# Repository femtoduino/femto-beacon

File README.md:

# femto-beacon
FemtoBeacon - Atmel SAM R21 (ARM Cortex M0+, SAM D21 with built in AT86RF233)

To contribute work, please do the following:

 - Fork https://github.com/femtoduino/femto-beacon
 - Checkout your fork of femto-beacon to your machine. You should now have something like `https://github.com/<your_username>/femto-beacon`
 - Add the femtoio/femto-beacon repository as the 'upstream' remote repository of your fork.

```
# Inside the checkout of your fork, add us as the remote repository named 'upstream'
git remote add upstream https://github.com/femtoduino/femto-beacon.git

# Remember to fetch from upstream to get all branch information
git fetch upstream
```

Now, you can pull the latest changes from 'upstream' into your fork, and push all work to your own fork
```
# To list branches.
git branch -a

# To pull changes from upstream 'master' branch into your 'master' branch (assuming you're in the master branch already)
git pull upstream master

# To switch into an existing branch named 'develop'
git checkout develop

# To create a new branch based on the develop branch
git checkout develop
# ...then, make sure you get the latest from upstream
git pull upstream develop
# ...now, create your new branch.
git checkout -b my-new-branch

# To push your new branch to your github fork
git push origin my-new-branch
```

...Once you push your changes to your fork, you may submit a Merge Request via github.
We will review and assess the changes before accepting or rejecting your changes.

## Requirements

For Arduino support, see https://github.com/femtoduino/ArduinoCore-atsamd21e18a/

For bare-metal programming, see below.

On Ubuntu machines, you will need Terry Guo's arm-none-eabi-* toolchain, along with the build-essentials package, openocd 0.9.x with cmsis-dap and hidapi-libusb enabled, and the BOSSA utility.

See the following on how to build OpenOCD on your machine: https://github.com/RIOT-OS/RIOT/wiki/OpenOCD
You must assert the required libraries are installed on your machine.

Compile OpenOCD with the following flags to enable cmsis-dap and hidapi support:
```
# Inside the openocd source code folder...
./configure --enable-maintainer-mode --enable-cmsis-dap --enable-hidapi-libusb
make
sudo make install
```

Install Eclipse C++, and the GNU ARM Eclipse plugins.

Install the BOSSA utility.

See https://github.com/shumatech/BOSSA

## Setup
Download the Atmel Software Framework into the libraries/ folder before compiling examples.
If you have the Atmel Software framework files in a directory named `asf-3.21.0`, then you would need it as `femto-beacon/libraries/asf-3.21.0`

Symlink the boards/femtobeacon folder into your copy of the ASF framework (libraries/asf-x.xx.x/sam0/boards/femtobeacon).
Symlink the femtoIO MPU9250 library folder into your copy of the ASF framework (libraries/asf-x.xx.x/thirdparty/MPU9250).

You can symlink the femto-beacon examples to your Eclipse workspace folder. For example, if you want to make the 'sam-r21-blink' project availabe in Eclipse:

```
# Use ~ or full path! Do not use ./
ln -s /path/to/femto-beacon/examples/sam-r21-blink /path/to/eclipse/workspace/sam-r21-blink
```

...Refresh the Project Explorer panel to view it as a project.

Update the example's config.mk file accordingly
```
# Path to top level ASF directory relative to this project directory.
PRJ_PATH = ../../libraries/asf-3.21.0
```

Then, open up the example in Eclipse, and build. This should generate a BIN file you can then upload to your board using the BOSSA shell.

## How to create a new project
Create a new C project in Eclipse, symlink the libraries/ folder from femto-beacon/libraries into your project's directory.
```
cd MyNewProject/
ln -s /path/to/femto-beacon/libraries libraries
```
You can then copy/modify the asf.h, config.mk, and Makefile into your new project. Remember to modify config.mk to include the paths of the ASF modules you wish to use.

## FemtoBeacon BT support (Nordic nRF52832 Bluetooth 4.2 + NFC, ARM Cortex M4L)
This board is unreleased at this time. These notes are here for future use.
For toolchain setup, see https://devzone.nordicsemi.com/tutorials/7/

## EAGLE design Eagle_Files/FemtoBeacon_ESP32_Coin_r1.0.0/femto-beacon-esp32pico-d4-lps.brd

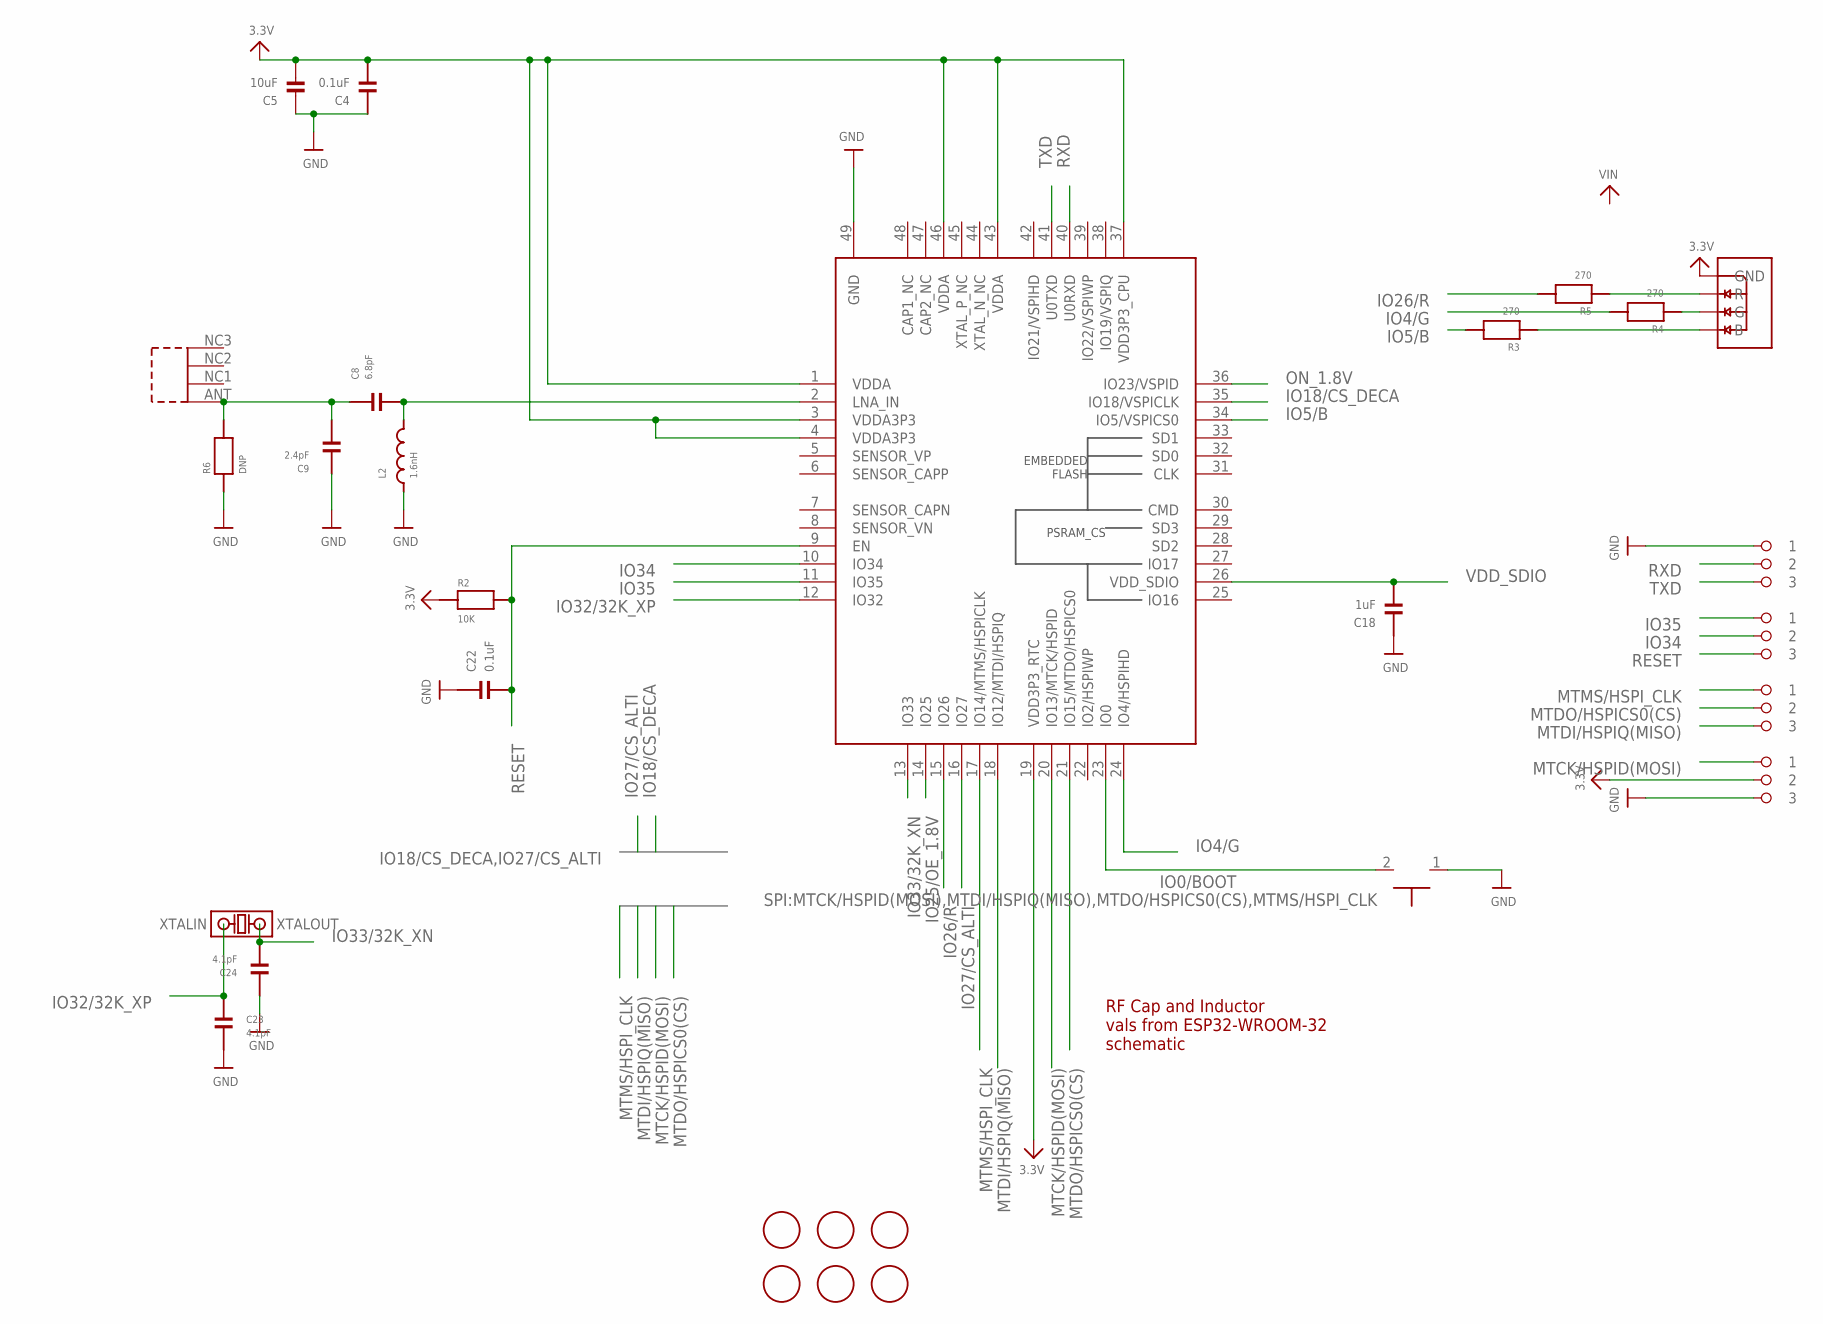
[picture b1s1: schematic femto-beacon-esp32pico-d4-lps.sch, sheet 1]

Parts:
ANT1: 0479480001
BOOT1: TACTILE_SWITCH_NO_GND_NO_BOSS; SIDE_ACT_NO_GND_NO_BOSS
C4, C22: 0.1uF; PART; MPN GRM033C80J104KE84D
C5: 10uF; _0603MP; MPN GRM188R61C106KAALD
C8: 6.8pF; PART; MPN GRM0335C2A6R8DA01D
C9: 2.4pF; PART; MPN GRM0335C1H2R4CA01D
C18: 1uF; PART; MPN CL03A105KQ3CSNH
C23, C24: 4.1pF; PART; MPN GRM0335C1H4R1BA01D
FID1, FID2, FID3, FID4, FID5, FID6: FIDUCIAL; FIDUCIAL_1MM
IC1: ESP32-PICO-D4; ESP32-QFN48_7X7
L2: 1.6nH; PART; MPN LQP03HQ1N6B02D
PIN_EN: 1X3_ROUND
PIN_GPIO_A: 1X3_ROUND
PIN_GPIO_B: 1X3_ROUND
PIN_UART: 1X3_ROUND
R2: 10K; PART; MPN RC0201JR-0710KL
R3, R4, R5: 270; PART; MPN RC0201FR-07270RL
R6: DNP; PART
RGB1: LRTB_R48G
XTAL2: ABS06-107-32.768KHZ-T

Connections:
3.3V: C4.2, C5.2, IC1.1 (VDDA), IC1.3 (VDDA3P3), IC1.4 (VDDA3P3), IC1.19 (VDD3P3_RTC), IC1.37 (VDD3P3_CPU), IC1.43 (VDDA), IC1.46 (VDDA), PIN_GPIO_A.P$2 (2), R2.1, RGB1.1 (GND); also elsewhere on the board
ANT: C8.2, IC1.2 (LNA_IN), L2.2
B_: R3.1, RGB1.4 (B)
GND: BOOT1.1, C4.1, C5.1, C9.1, C18.1, C22.1, C23.1, C24.2, IC1.49 (GND), L2.1, PIN_GPIO_A.P$3 (3), PIN_UART.P$1 (1), R6.1; also elsewhere on the board
G_: R4.1, RGB1.3 (G)
IO0/BOOT: BOOT1.2, IC1.23 (IO0)
IO4/G: IC1.24 (IO4/HSPIHD), R4.2
IO5/B: IC1.34 (IO5/VSPICS0), R3.2
IO18/CS_DECA: IC1.35 (IO18/VSPICLK); also elsewhere on the board
IO25/OE_1.8V: IC1.14 (IO25); also elsewhere on the board
IO26/R: IC1.15 (IO26), R5.2
IO27/CS_ALTI: IC1.16 (IO27); also elsewhere on the board
IO32/32K_XP: C23.2, IC1.12 (IO32), XTAL2.1 (XTALIN)
IO33/32K_XN: C24.1, IC1.13 (IO33), XTAL2.2 (XTALOUT)
IO34: IC1.10 (IO34), PIN_EN.P$2 (2)
IO35: IC1.11 (IO35), PIN_EN.P$1 (1)
MTCK/HSPID(MOSI): IC1.20 (IO13/MTCK/HSPID), PIN_GPIO_A.P$1 (1); also elsewhere on the board
MTDI/HSPIQ(MISO): IC1.18 (IO12/MTDI/HSPIQ), PIN_GPIO_B.P$3 (3); also elsewhere on the board
MTDO/HSPICS0(CS): IC1.21 (IO15/MTDO/HSPICS0), PIN_GPIO_B.P$2 (2); also elsewhere on the board
MTMS/HSPI_CLK: IC1.17 (IO14/MTMS/HSPICLK), PIN_GPIO_B.P$1 (1); also elsewhere on the board
unnamed: ANT1.ANT (1), C8.1, C9.2, R6.2
ON_1.8V: IC1.36 (IO23/VSPID); also elsewhere on the board
RESET: C22.2, IC1.9 (EN), PIN_EN.P$3 (3), R2.2
RXD: IC1.40 (U0RXD), PIN_UART.P$2 (2)
R_: R5.1, RGB1.2 (R)
TXD: IC1.41 (U0TXD), PIN_UART.P$3 (3)
VDD_SDIO: C18.2, IC1.26 (VDD_SDIO)

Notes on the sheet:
RF Cap and Inductor vals from ESP32-WROOM-32 schematic

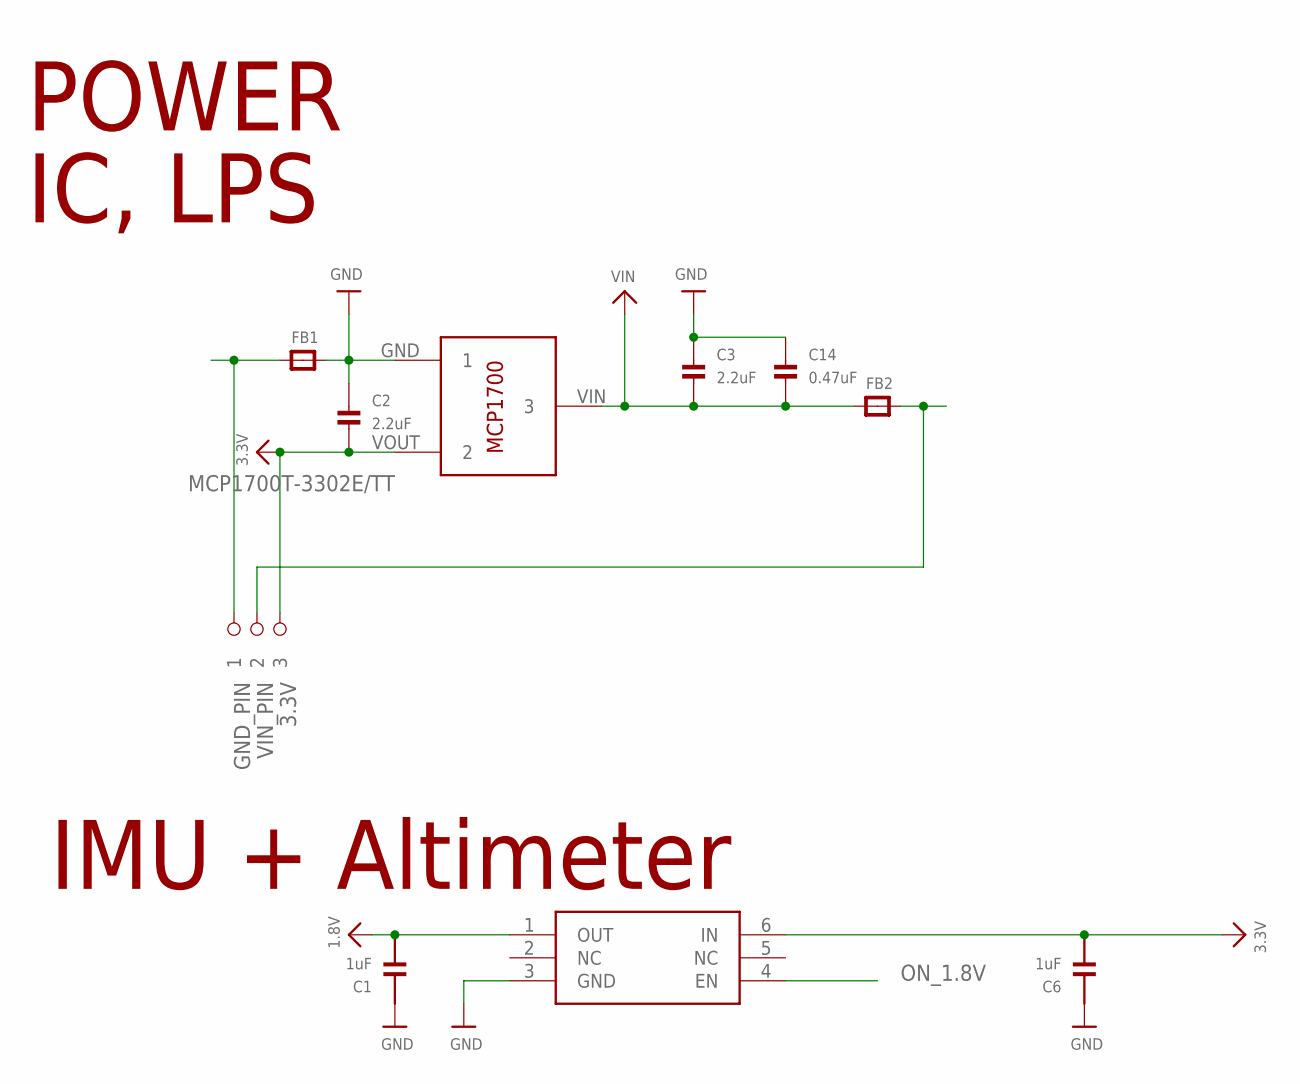
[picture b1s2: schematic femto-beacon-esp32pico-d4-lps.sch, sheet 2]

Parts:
C1, C6: 1uF; PART; MPN CL03A105KQ3CSNH
C2, C3: 2.2uF; _0402MP; MPN C1005X5R0J225K050BC
C14: 0.47uF; _0402MP; MPN GRM155R60J474KE19D
FB1, FB2: FERRITE_0603MP; _0603MP
LDO1: MCP1700T-3302E/TT
LDO1.8V: NCP705MT18TCG; CASE_511BR; MPN NCP705MT18TCG
PIN_PWR: 1X3_ROUND

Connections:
1.8V: C1.2, LDO1.8V.1 (OUT); also elsewhere on the board
3.3V: C2.2, C6.2, LDO1.VOUT (2), LDO1.8V.6 (IN), PIN_PWR.P$3 (3); also elsewhere on the board
GND: C1.1, C2.1, C3.1, C6.1, C14.1, FB1.2, LDO1.GND (1), LDO1.8V.3 (GND); also elsewhere on the board
GND_PIN: FB1.1, PIN_PWR.P$1 (1)
ON_1.8V: LDO1.8V.4 (EN); also elsewhere on the board
VIN: C3.2, C14.2, FB2.1, LDO1.VIN (3)
VIN_PIN: FB2.2, PIN_PWR.P$2 (2)

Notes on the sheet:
POWER
IC, LPS
IMU + Altimeter

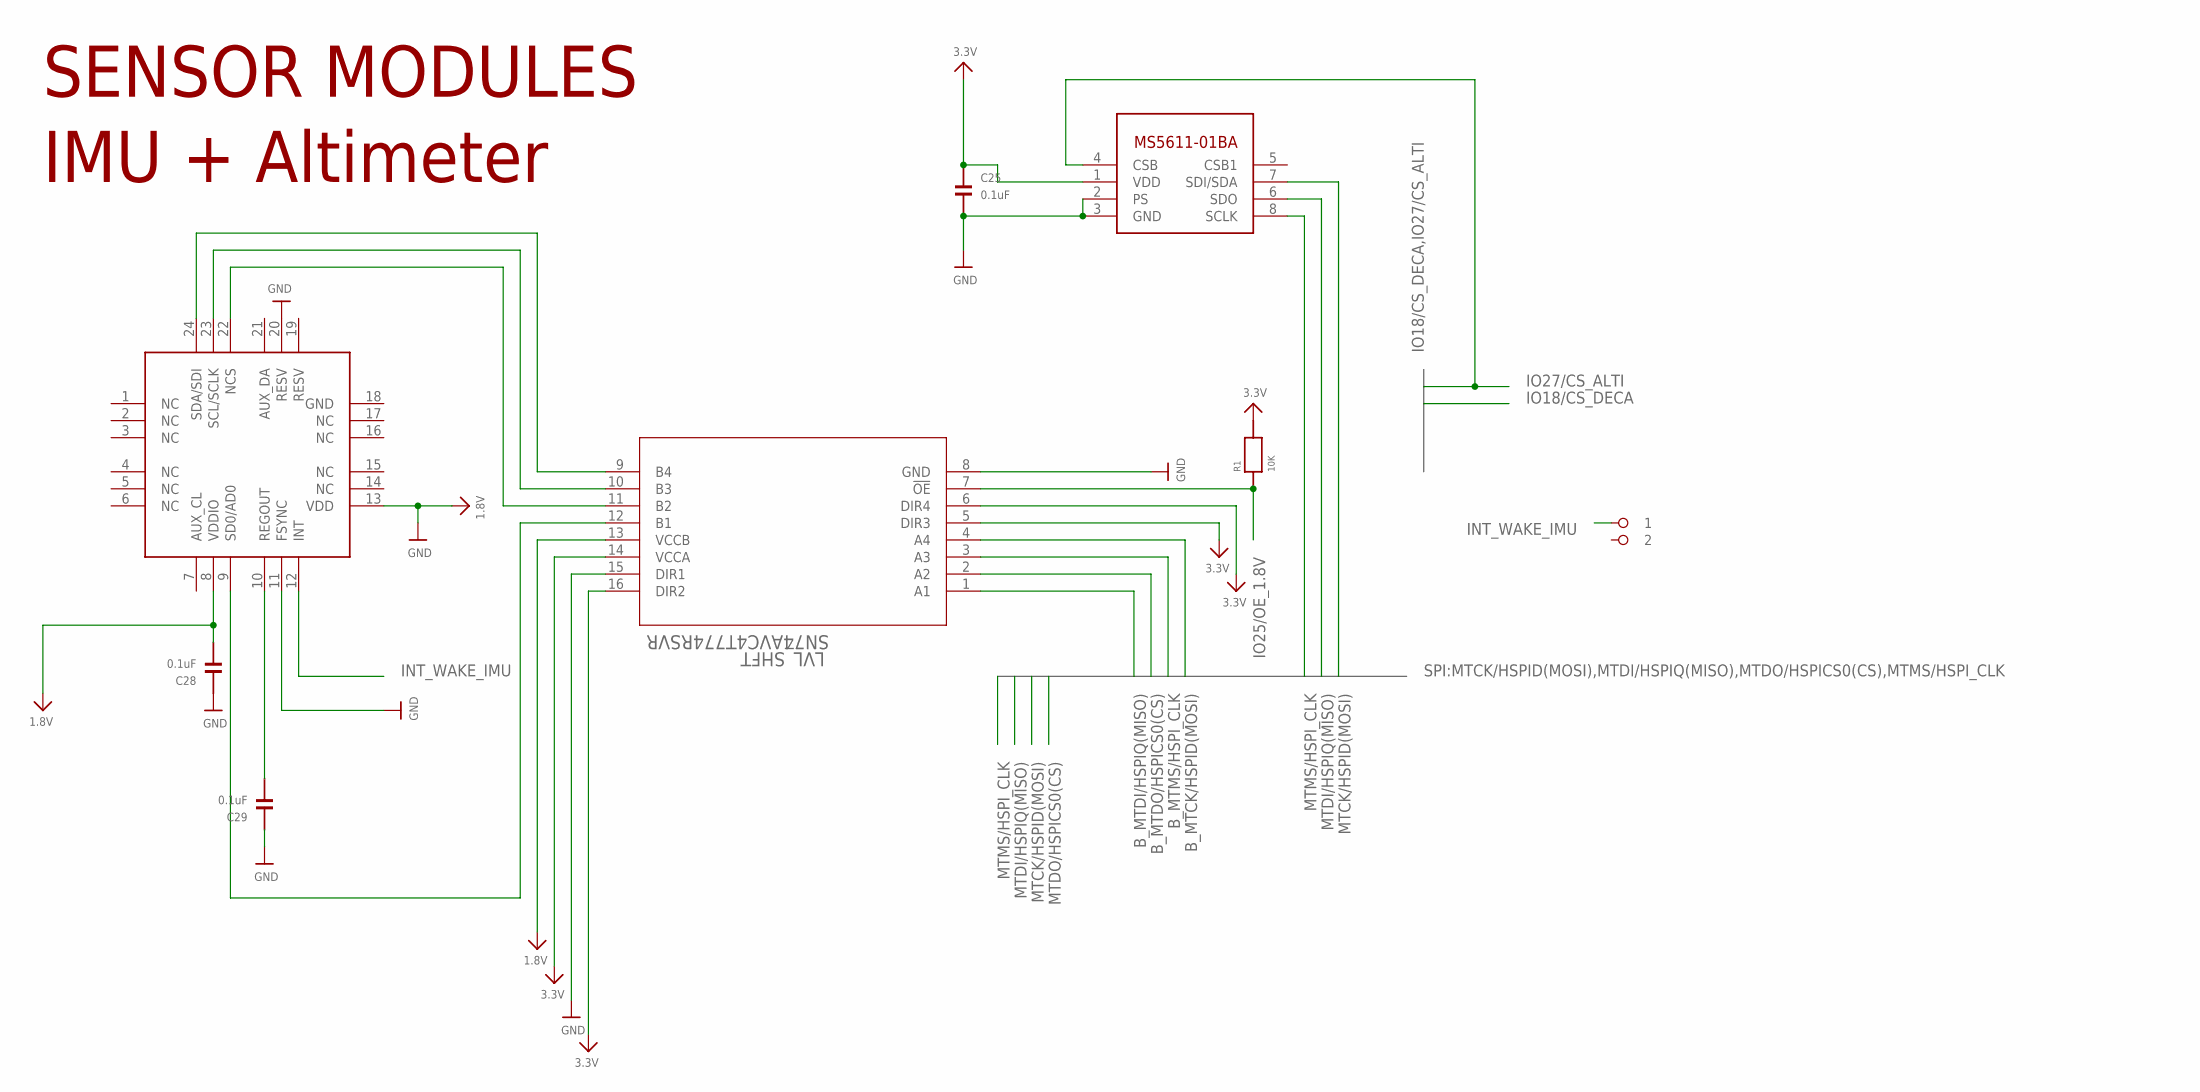
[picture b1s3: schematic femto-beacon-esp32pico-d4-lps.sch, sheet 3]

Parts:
ALT1: MS5611-01BA03; MPN MS561101BA03-50
C25, C28, C29: 0.1uF; PART; MPN GRM033C80J104KE84D
IMU1: ICM-20948; QFN24_3X3
LVL_SHFT: SN74AVC4T774RSVR; RSV16; MPN SN74AVC4T774RSVR
R1: 10K; PART; MPN RC0201JR-0710KL
U$1: 1X2_ROUND

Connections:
1.8V: C28.2, IMU1.8 (VDDIO), IMU1.13 (VDD), LVL_SHFT.13 (VCCB); also elsewhere on the board
3.3V: ALT1.1 (VDD), C25.1, LVL_SHFT.5 (DIR3), LVL_SHFT.6 (DIR4), LVL_SHFT.14 (VCCA), LVL_SHFT.16 (DIR2), R1.2; also elsewhere on the board
B_MTCK/HSPID(MOSI): IMU1.24 (SDA/SDI), LVL_SHFT.9 (B4)
B_MTDI/HSPIQ(MISO): IMU1.9 (SD0/AD0), LVL_SHFT.12 (B1)
B_MTDO/HSPICS0(CS): IMU1.22 (NCS), LVL_SHFT.11 (B2)
B_MTMS/HSPI_CLK: IMU1.23 (SCL/SCLK), LVL_SHFT.10 (B3)
GND: ALT1.2 (PS), ALT1.3 (GND), C25.2, C28.1, C29.1, IMU1.11 (FSYNC), IMU1.18 (GND), IMU1.20 (RESV), LVL_SHFT.8 (GND), LVL_SHFT.15 (DIR1); also elsewhere on the board
INT_WAKE_IMU: IMU1.12 (INT), U$1.P$1 (1)
IO25/OE_1.8V: LVL_SHFT.7 (!OE), R1.1; also elsewhere on the board
IO27/CS_ALTI: ALT1.4 (CSB); also elsewhere on the board
MTCK/HSPID(MOSI): ALT1.7 (SDI/SDA), LVL_SHFT.4 (A4); also elsewhere on the board
MTDI/HSPIQ(MISO): ALT1.6 (SDO), LVL_SHFT.1 (A1); also elsewhere on the board
MTDO/HSPICS0(CS): LVL_SHFT.2 (A2); also elsewhere on the board
MTMS/HSPI_CLK: ALT1.8 (SCLK), LVL_SHFT.3 (A3); also elsewhere on the board
unnamed: C29.2, IMU1.10 (REGOUT)

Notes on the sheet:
SENSOR MODULES
IMU + Altimeter

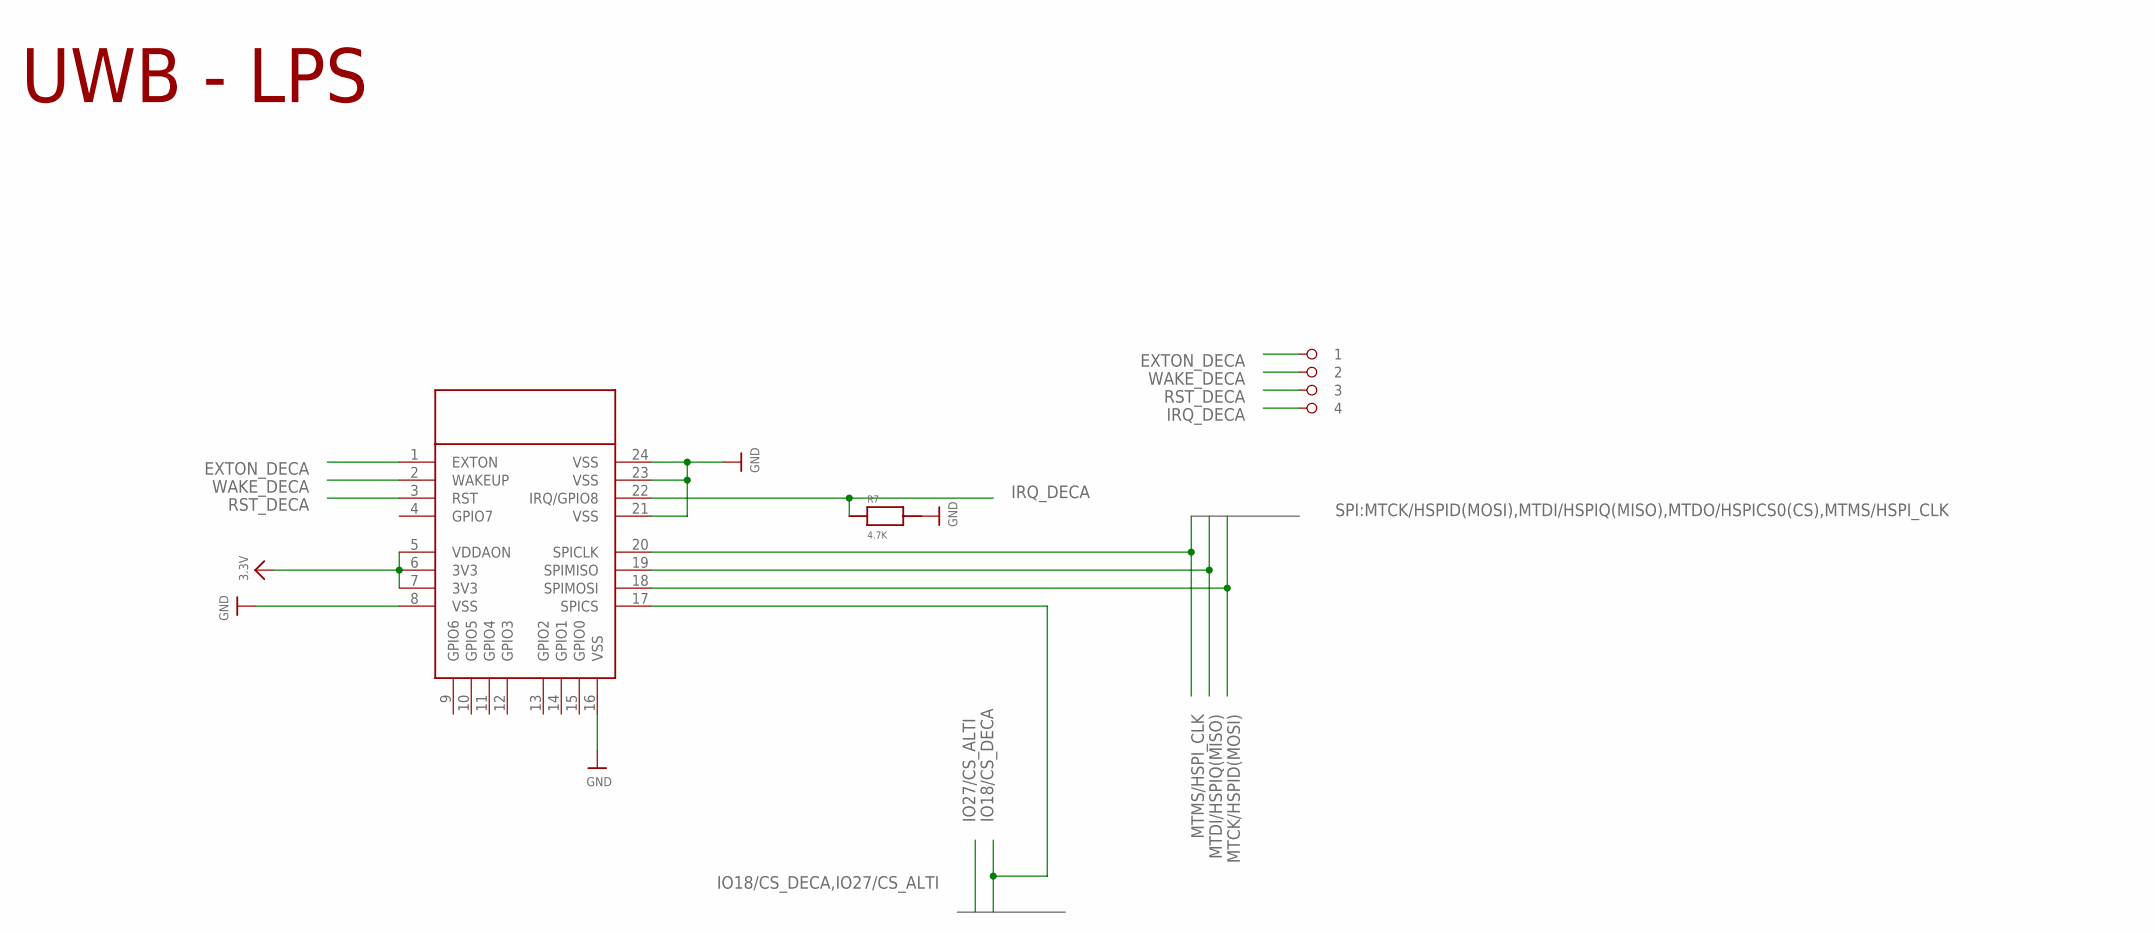
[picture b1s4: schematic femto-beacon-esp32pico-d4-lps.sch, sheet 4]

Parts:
LPS1: DWM100; DWM100_MOD
R7: 4.7K; PART; MPN RC0201FR-074K7L
U$39: 1X4_ROUND

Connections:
3.3V: LPS1.5 (VDDAON), LPS1.6 (3V3), LPS1.7 (3V3); also elsewhere on the board
EXTON_DECA: LPS1.1 (EXTON), U$39.P$1 (1)
GND: LPS1.8 (VSS), LPS1.16 (VSS), LPS1.21 (VSS), LPS1.23 (VSS), LPS1.24 (VSS), R7.2; also elsewhere on the board
IO18/CS_DECA: LPS1.17 (SPICS); also elsewhere on the board
IRQ_DECA: LPS1.22 (IRQ/GPIO8), R7.1, U$39.P$4 (4)
MTCK/HSPID(MOSI): LPS1.18 (SPIMOSI); also elsewhere on the board
MTDI/HSPIQ(MISO): LPS1.19 (SPIMISO); also elsewhere on the board
MTMS/HSPI_CLK: LPS1.20 (SPICLK); also elsewhere on the board
RST_DECA: LPS1.3 (RST), U$39.P$3 (3)
WAKE_DECA: LPS1.2 (WAKEUP), U$39.P$2 (2)

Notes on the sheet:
UWB - LPS

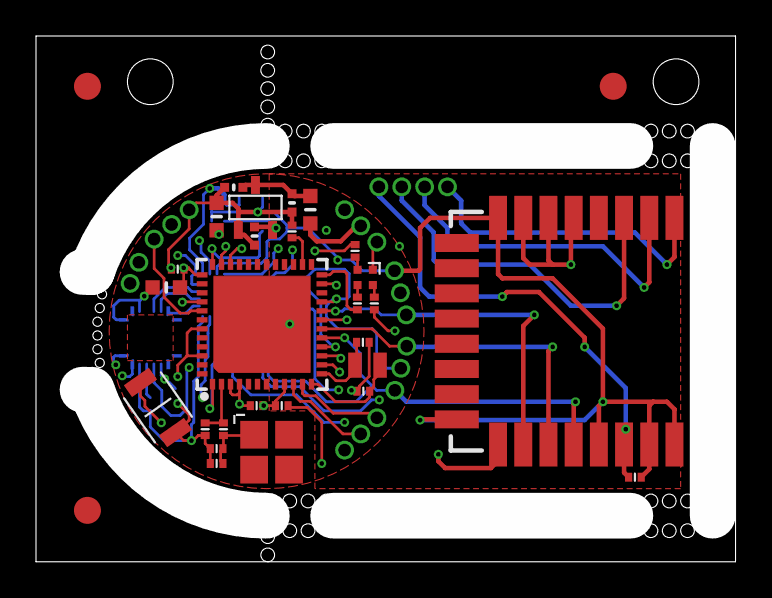
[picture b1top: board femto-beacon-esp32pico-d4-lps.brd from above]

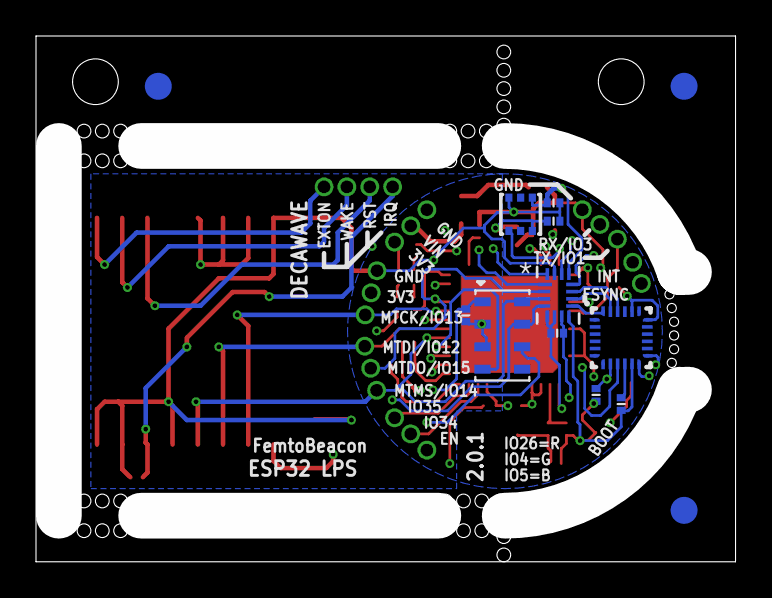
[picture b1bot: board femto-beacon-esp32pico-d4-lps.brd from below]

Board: 4 copper layers, 38.9 x 29.2 mm, 50 parts (13 on the bottom side), 41 nets.

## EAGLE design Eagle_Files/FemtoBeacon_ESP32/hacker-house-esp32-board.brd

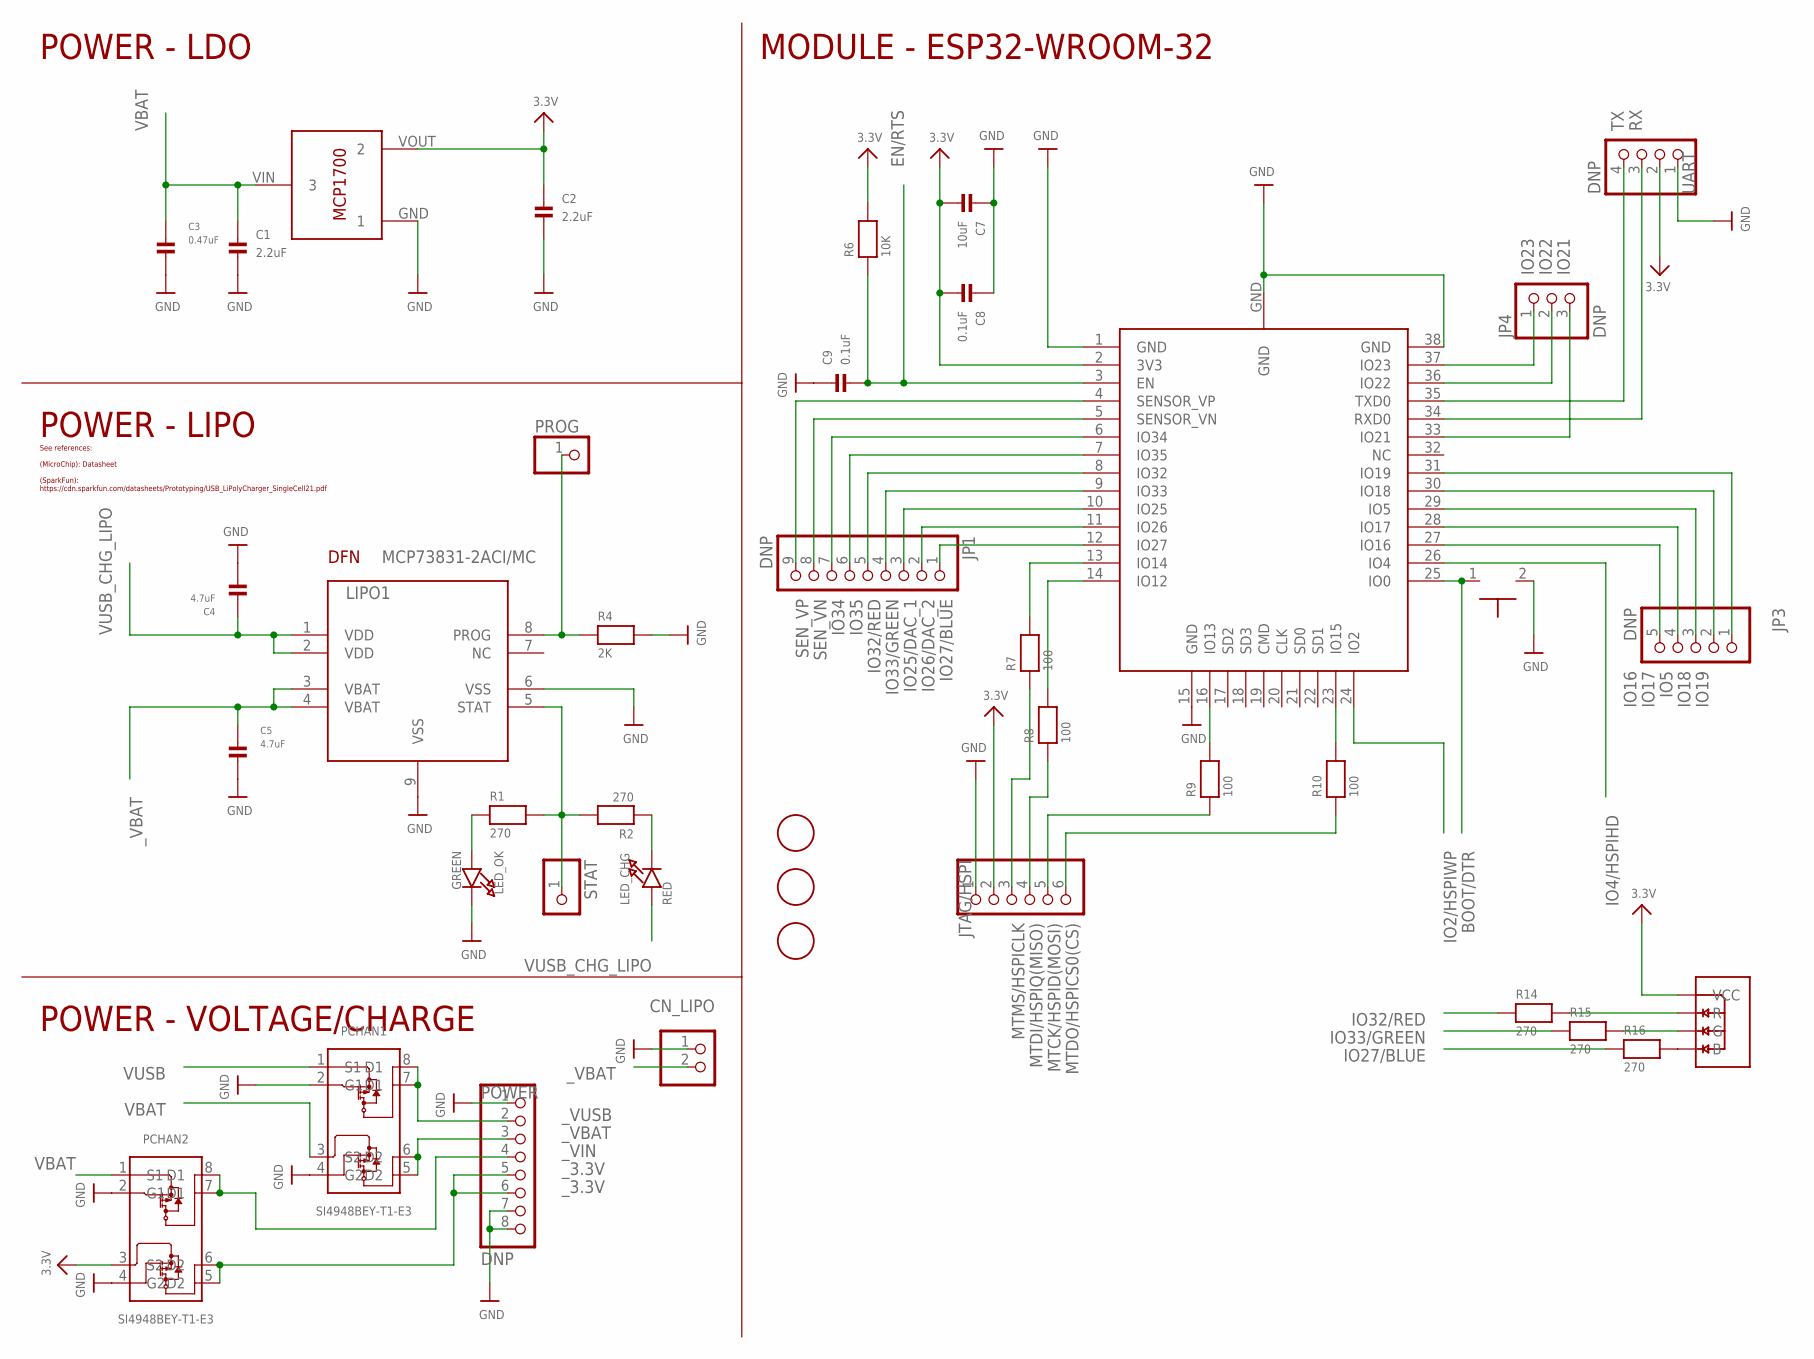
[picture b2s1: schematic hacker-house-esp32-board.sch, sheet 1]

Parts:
BOOT: TACTILE_SWITCH_NO_GND_NO_BOSS; SIDE_ACT_NO_GND_NO_BOSS
C1, C2: 2.2uF; _0402MP; MPN C1005X5R0J225K050BC
C3: 0.47uF; _0402MP; MPN GRM155R60J474KE19D
C4, C5: 4.7uF; _0402MP; MPN GRM155R60G475ME47D
C7: 10uF; _0603MP; MPN C1608X5R1A106K080AC
C8, C9: 0.1uF; _0402MP; MPN CC0402KRX7R6BB104
CN_LIPO: JST_2PIN; JSTPH2
FID1, FID2, FID3: FIDUCIAL; FIDUCIAL_1MM
JP1: DNP; 1X09
JP3: DNP; 1X05
JP4: DNP; 1X03
JTAG/HSPI: HEADER-1X6ROUND; 1X06_ROUND
LDO1: 3.3V; MCP1700T-3302E/TT
LED_CHG: RED; CHIPLED_0603_NOOUTLINE; MPN 350-2029-1-ND
LED_OK: GREEN; CHIPLED_0603_NOOUTLINE; MPN 350-2035-1-ND
LIPO1: MCP73831-2ACI/MC; 2X3_DFN
MOD1: ESP32-WROOM-32; ESP32-WROOM-32-MODULE; MPN ESP32-WROOM-32D
PCHAN1, PCHAN2: SI4948BEY-T1-E3; SO-8
POWER: DNP; 1X08_OVAL
PROG: HEADER-1X1ROUND; 1X01_ROUND
R1, R2, R14, R15, R16: 270; _0402MP; MPN CRCW0402270RFKED
R4: 2K; _0402MP; MPN CPF0402B2K0E1
R6: 10K; _0402MP; MPN CRCW040210K0FKED
R7, R8, R9, R10: 100; _0402MP; MPN CPF0402B100RE1
RGB1: LRTB_R48G
STAT: HEADER-1X1ROUND; 1X01_ROUND
UART: DNP; 1X04_ROUND

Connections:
3.3V: C2.1, C7.2, C8.2, JTAG/HSPI.2, LDO1.VOUT (2), MOD1.2 (3V3), PCHAN2.3 (S2), R6.2, RGB1.1 (VCC), UART.2; also elsewhere on the board
BOOT/DTR: BOOT.1, MOD1.25 (IO0); also elsewhere on the board
EN/RTS: C9.2, MOD1.3 (EN), R6.1; also elsewhere on the board
GND_UNMASKED: BOOT.2, C1.2, C2.2, C3.2, C4.2, C5.2, C7.1, C8.1, C9.1, CN_LIPO.1, JTAG/HSPI.1, LDO1.GND (1), LED_OK.C, LIPO1.6 (VSS), LIPO1.9 (VSS), MOD1.1 (GND), MOD1.15 (GND), MOD1.38 (GND), MOD1.GND, PCHAN1.2 (G1), PCHAN1.4 (G2), PCHAN2.2 (G1), PCHAN2.4 (G2), POWER.1, POWER.7, POWER.8, R4.2, UART.1; also elsewhere on the board
IO2/HSPIWP: MOD1.24 (IO2)
IO4/HSPIHD: MOD1.26 (IO4)
IO5: JP3.3, MOD1.29 (IO5)
IO16: JP3.5, MOD1.27 (IO16)
IO17: JP3.4, MOD1.28 (IO17)
IO18: JP3.2, MOD1.30 (IO18)
IO19: JP3.1, MOD1.31 (IO19)
IO21: JP4.3, MOD1.33 (IO21)
IO22: JP4.2, MOD1.36 (IO22)
IO23: JP4.1, MOD1.37 (IO23)
IO25/DAC_1: JP1.3, MOD1.10 (IO25)
IO26/DAC_2: JP1.2, MOD1.11 (IO26)
IO27/BLUE: JP1.1, MOD1.12 (IO27), R16.1
IO32/RED: JP1.5, MOD1.8 (IO32), R14.1
IO33/GREEN: JP1.4, MOD1.9 (IO33), R15.1
IO34: JP1.7, MOD1.6 (IO34)
IO35: JP1.6, MOD1.7 (IO35)
MTCK/HSPID(MOSI): JTAG/HSPI.5, R9.1
MTDI/HSPIQ(MISO): JTAG/HSPI.4, R8.1
MTDI_: MOD1.14 (IO12), R8.2
MTDO/HSPICS0(CS): JTAG/HSPI.6, R10.1
MTMS/HSPICLK: JTAG/HSPI.3, R7.1
unnamed: R16.2, RGB1.4 (B)
unnamed: MOD1.13 (IO14), R7.2
unnamed: R15.2, RGB1.3 (G)
unnamed: LED_OK.A, R1.1
unnamed: LED_CHG.C, R2.1
unnamed: R14.2, RGB1.2 (R)
unnamed: MOD1.16 (IO13), R9.2
unnamed: MOD1.23 (IO15), R10.2
PROG: LIPO1.8 (PROG), PROG.1, R4.1
RX: MOD1.34 (RXD0), UART.3; also elsewhere on the board
SEN_VN: JP1.8, MOD1.5 (SENSOR_VN)
SEN_VP: JP1.9, MOD1.4 (SENSOR_VP)
STAT: LIPO1.5 (STAT), R1.2, R2.2, STAT.1
TX: MOD1.35 (TXD0), UART.4; also elsewhere on the board
VBAT: C1.1, C3.1, LDO1.VIN (3), PCHAN1.3 (S2), PCHAN2.1 (S1)
VUSB: PCHAN1.1 (S1); also elsewhere on the board
VUSB_CHG_LIPO: C4.1, LED_CHG.A, LIPO1.1 (VDD), LIPO1.2 (VDD); also elsewhere on the board
_3.3V: PCHAN2.5 (D2), PCHAN2.6 (D2), POWER.5, POWER.6
_VBAT: C5.1, CN_LIPO.2, LIPO1.3 (VBAT), LIPO1.4 (VBAT), PCHAN1.5 (D2), PCHAN1.6 (D2), POWER.3
_VIN: PCHAN2.7 (D1), PCHAN2.8 (D1), POWER.4
_VUSB: PCHAN1.7 (D1), PCHAN1.8 (D1), POWER.2; also elsewhere on the board

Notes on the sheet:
POWER - LDO
POWER - LIPO
POWER - VOLTAGE/CHARGE
MODULE - ESP32-WROOM-32
See references: (MicroChip): Datasheet (SparkFun): https://cdn.sparkfun.com/datasheets/Prototyping/USB_LiPolyCharger_SingleCell21.pdf

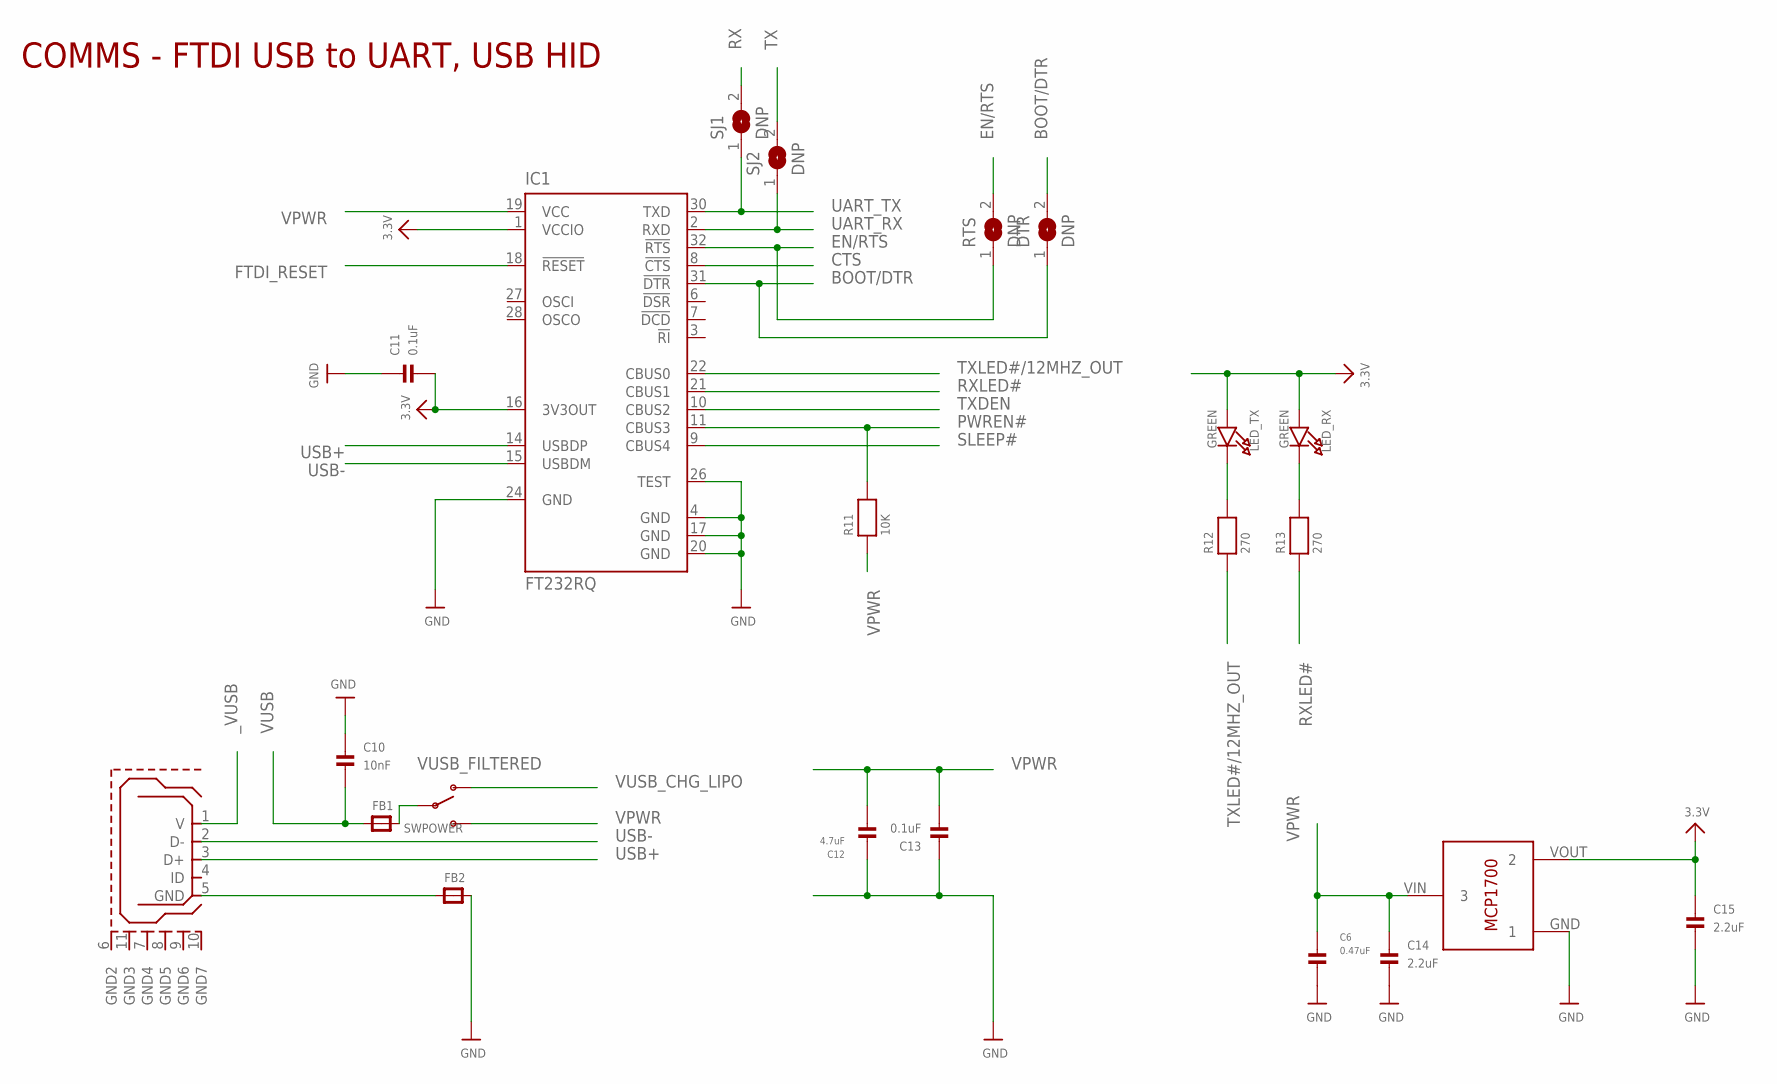
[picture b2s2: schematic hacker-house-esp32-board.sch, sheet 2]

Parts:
C6: 0.47uF; _0402MP; MPN GRM155R60J474KE19D
C10: 10nF; _0402MP; MPN GRM155R71E103KA01D
C11, C13: 0.1uF; _0402MP; MPN CC0402KRX7R6BB104
C12: 4.7uF; _0402MP; MPN GRM155R60G475ME47D
C14, C15: 2.2uF; _0402MP; MPN C1005X5R0J225K050BC
DTR: DNP; SOLDERJUMPER_CLOSEDWIRE
FB1, FB2: FERRITE_0603MP; _0603MP
IC1: FT232RQ; QFN32; MPN FT232RQ-REEL
LDO2: 3.3V; MCP1700T-3302E/TT
LED_RX: GREEN; CHIPLED_0603_NOOUTLINE; MPN 350-2035-1-ND
LED_TX: GREEN; CHIPLED_0603_NOOUTLINE; MPN 350-2035-1-ND
R11: 10K; _0402MP; MPN CRCW040210K0FKED
R12, R13: 270; _0402MP; MPN CRCW0402270RFKED
RTS: DNP; SOLDERJUMPER_CLOSEDWIRE
SJ1, SJ2: DNP; SOLDERJUMPER_CLOSEDWIRE
SWPOWER: SWITCH_SPDT; SPDT_SMT_SSSS811101
U$14: USB_MICROB; USB_MICROB_PACKAGE; MPN ZX62-B-5PA(33)

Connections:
3.3V: C11.2, C15.1, IC1.1 (VCCIO), IC1.16 (3V3OUT), LDO2.VOUT (2), LED_RX.A, LED_TX.A; also elsewhere on the board
BOOT/DTR: DTR.1, DTR.2, IC1.31 (!DTR); also elsewhere on the board
CTS: IC1.8 (!CTS)
EN/RTS: IC1.32 (!RTS), RTS.1, RTS.2; also elsewhere on the board
FTDI_RESET: IC1.18 (!RESET)
GND_UNMASKED: C6.2, C10.1, C11.1, C12.1, C13.1, C14.2, C15.2, FB2.2, IC1.4 (GND), IC1.17 (GND), IC1.20 (GND), IC1.24 (GND), IC1.26 (TEST), LDO2.GND (1); also elsewhere on the board
unnamed: FB2.1, U$14.5 (GND)
unnamed: LED_TX.C, R12.2
unnamed: LED_RX.C, R13.2
PWREN#: IC1.11 (CBUS3), R11.2
RX: SJ1.2; also elsewhere on the board
RXLED#: IC1.21 (CBUS1), R13.1
SLEEP#: IC1.9 (CBUS4)
TX: SJ2.2; also elsewhere on the board
TXDEN: IC1.10 (CBUS2)
TXLED#/12MHZ_OUT: IC1.22 (CBUS0), R12.1
UART_RX: IC1.2 (RXD), SJ2.1
UART_TX: IC1.30 (TXD), SJ1.1
USB+: IC1.14 (USBDP), U$14.3 (D+)
USB-: IC1.15 (USBDM), U$14.2 (D-)
VPWR: C6.1, C12.2, C13.2, C14.1, IC1.19 (VCC), LDO2.VIN (3), R11.1, SWPOWER.C (S)
VUSB: C10.2, FB1.1; also elsewhere on the board
VUSB_CHG_LIPO: SWPOWER.A (O); also elsewhere on the board
VUSB_FILTERED: FB1.2, SWPOWER.B
_VUSB: U$14.1 (V); also elsewhere on the board

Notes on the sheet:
COMMS - FTDI USB to UART, USB HID

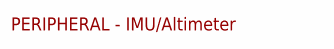
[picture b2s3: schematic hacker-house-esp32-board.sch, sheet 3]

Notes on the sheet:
PERIPHERAL - IMU/Altimeter

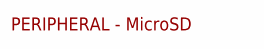
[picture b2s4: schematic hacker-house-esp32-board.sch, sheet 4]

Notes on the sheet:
PERIPHERAL - MicroSD

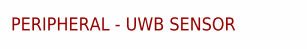
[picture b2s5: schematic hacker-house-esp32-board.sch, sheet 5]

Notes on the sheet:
PERIPHERAL - UWB SENSOR

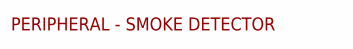
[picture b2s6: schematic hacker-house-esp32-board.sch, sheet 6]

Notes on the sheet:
PERIPHERAL - SMOKE DETECTOR

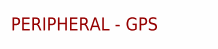
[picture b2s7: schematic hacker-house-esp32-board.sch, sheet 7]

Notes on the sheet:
PERIPHERAL - GPS

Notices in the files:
parts and their libraries:
microbuilder: This work is placed in the public domain, and may be freely used for commercial and non-commercial work with the following conditions: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
